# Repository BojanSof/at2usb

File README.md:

# AT (PS/2) keyboard to USB converter

PIC16F1459 solution for converting old AT (PS/2) keyboard to USB.

## Hardware

Schematic and one layer PCB can be found under `hardware` directory.
The hardware design is created using KiCad 7.0.
The circuit is very simple and it can be created easily on prototyping board.

## Firmware

The firmware is developed with MPLAB X IDE, found under `at2usbClassic.X` directory.
USB stack implementation and main HID app code is based on USB HID keyboard project from [Microchip Libraries for Applications (MLA)](https://www.microchip.com/en-us/tools-resources/develop/libraries/microchip-libraries-for-applications).

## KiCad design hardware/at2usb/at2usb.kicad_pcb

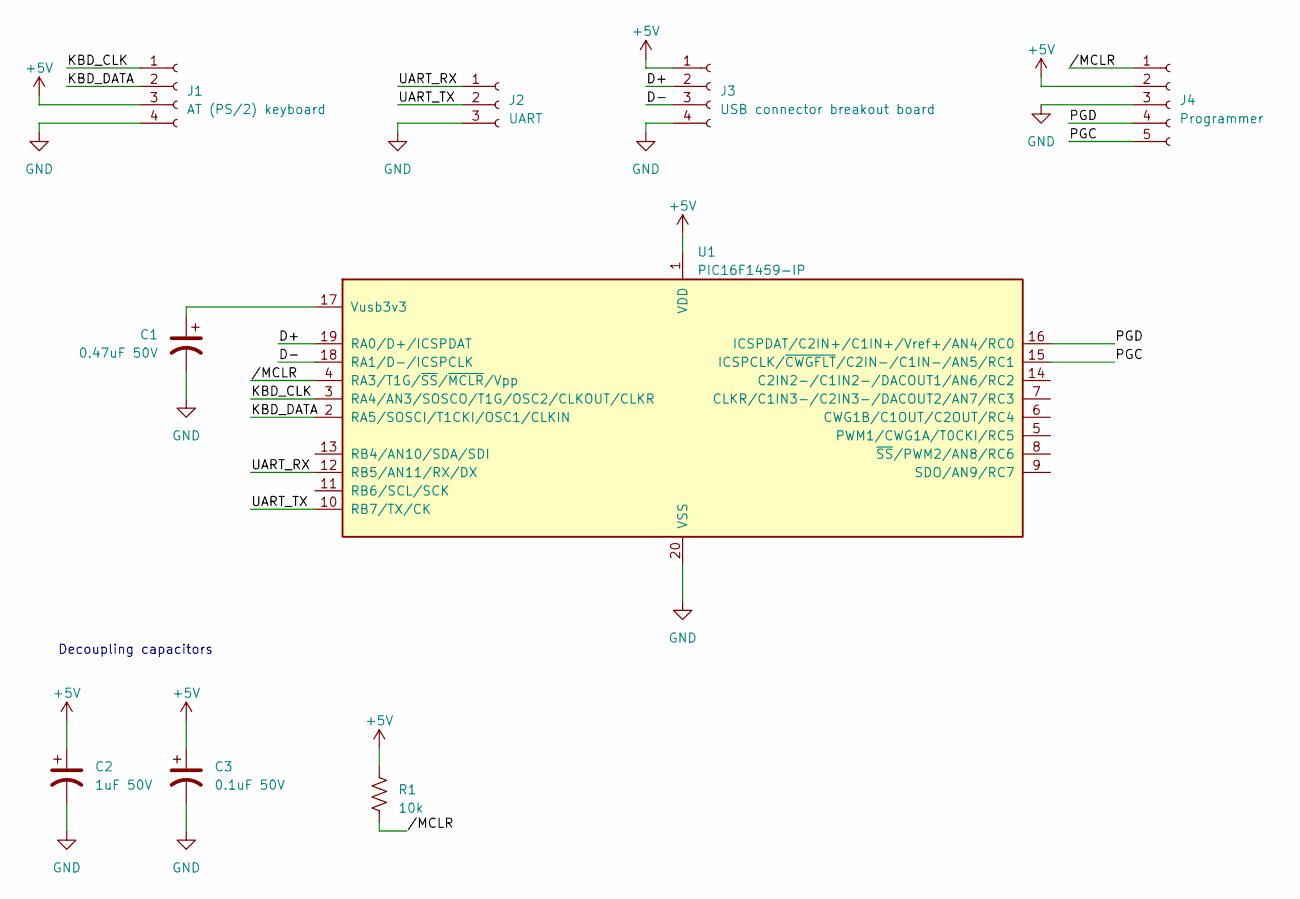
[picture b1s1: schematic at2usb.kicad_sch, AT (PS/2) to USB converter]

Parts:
C1: 0.47uF 50V; CP_Radial_D5.0mm_P2.00mm
C2: 1uF 50V; CP_Radial_D5.0mm_P2.00mm
C3: 0.1uF 50V; CP_Radial_D5.0mm_P2.00mm
J1: AT (PS/2) keyboard; PinHeader_1x04_P2.54mm_Vertical
J2: UART; PinHeader_1x03_P2.54mm_Vertical
J3: USB connector breakout board; PinHeader_1x04_P2.54mm_Vertical
J4: Programmer; PinHeader_1x05_P2.54mm_Vertical
R1: 10k; R_Axial_DIN0207_L6.3mm_D2.5mm_P2.54mm_Vertical
U1: PIC16F1459-IP; DIP-20_W7.62mm_Socket

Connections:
+5V: C2.1, C3.1, J1.3, J3.1, J4.2, R1.1, U1.1 (VDD)
/D+: J3.2, U1.19 (RA0/D+/ICSPDAT)
/D-: J3.3, U1.18 (RA1/D-/ICSPCLK)
/KBD_CLK: J1.1, U1.3 (RA4/AN3/SOSCO/T1G/OSC2/CLKOUT/CLKR)
/KBD_DATA: J1.2, U1.2 (RA5/SOSCI/T1CKI/OSC1/CLKIN)
/PGC: J4.5, U1.15 (ICSPCLK/~CWGFLT/C2IN-/C1IN-/AN5/RC1)
/PGD: J4.4, U1.16 (ICSPDAT/C2IN+/C1IN+/Vref+/AN4/RC0)
/UART_RX: J2.1, U1.12 (RB5/AN11/RX/DX)
/UART_TX: J2.2, U1.10 (RB7/TX/CK)
//MCLR: J4.1, R1.2, U1.4 (RA3/T1G/~SS/~MCLR/Vpp)
GND: C1.2, C2.2, C3.2, J1.4, J2.3, J3.4, J4.3, U1.20 (VSS)
unnamed: C1.1, U1.17 (Vusb3v3)

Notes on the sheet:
Decoupling capacitors

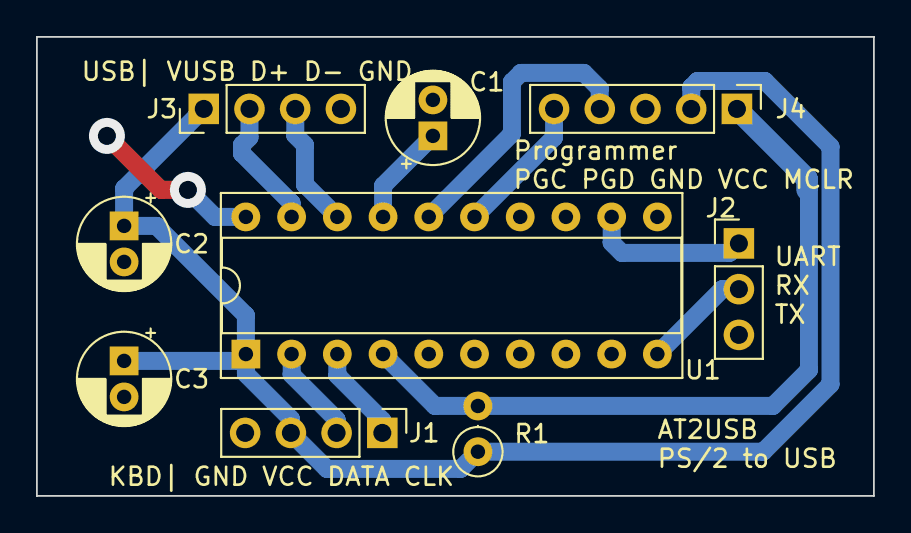
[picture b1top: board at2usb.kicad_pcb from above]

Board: 2 copper layers, 46.5 x 25.5 mm, 9 parts (0 on the bottom side), 12 nets.

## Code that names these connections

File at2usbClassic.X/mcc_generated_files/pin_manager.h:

/**
  @Generated Pin Manager Header File

  @Company:
    Microchip Technology Inc.

  @File Name:
    pin_manager.h

  @Summary:
    This is the Pin Manager file generated using PIC10 / PIC12 / PIC16 / PIC18 MCUs

  @Description
    This header file provides APIs for driver for .
    Generation Information :
        Product Revision  :  PIC10 / PIC12 / PIC16 / PIC18 MCUs - 1.81.8
        Device            :  PIC16F1459
        Driver Version    :  2.11
    The generated drivers are tested against the following:
        Compiler          :  XC8 2.36 and above
        MPLAB 	          :  MPLAB X 6.00	
*/

/*
    (c) 2018 Microchip Technology Inc. and its subsidiaries. 
    
    Subject to your compliance with these terms, you may use Microchip software and any 
    derivatives exclusively with Microchip products. It is your responsibility to comply with third party 
    license terms applicable to your use of third party software (including open source software) that 
    may accompany Microchip software.
    
    THIS SOFTWARE IS SUPPLIED BY MICROCHIP "AS IS". NO WARRANTIES, WHETHER 
    EXPRESS, IMPLIED OR STATUTORY, APPLY TO THIS SOFTWARE, INCLUDING ANY 
    IMPLIED WARRANTIES OF NON-INFRINGEMENT, MERCHANTABILITY, AND FITNESS 
    FOR A PARTICULAR PURPOSE.
    
    IN NO EVENT WILL MICROCHIP BE LIABLE FOR ANY INDIRECT, SPECIAL, PUNITIVE, 
    INCIDENTAL OR CONSEQUENTIAL LOSS, DAMAGE, COST OR EXPENSE OF ANY KIND 
    WHATSOEVER RELATED TO THE SOFTWARE, HOWEVER CAUSED, EVEN IF MICROCHIP 
    HAS BEEN ADVISED OF THE POSSIBILITY OR THE DAMAGES ARE FORESEEABLE. TO 
    THE FULLEST EXTENT ALLOWED BY LAW, MICROCHIP'S TOTAL LIABILITY ON ALL 
    CLAIMS IN ANY WAY RELATED TO THIS SOFTWARE WILL NOT EXCEED THE AMOUNT 
    OF FEES, IF ANY, THAT YOU HAVE PAID DIRECTLY TO MICROCHIP FOR THIS 
    SOFTWARE.
*/

#ifndef PIN_MANAGER_H
#define PIN_MANAGER_H

/**
  Section: Included Files
*/

#include <xc.h>

#define INPUT   1
#define OUTPUT  0

#define HIGH    1
#define LOW     0

#define ANALOG      1
#define DIGITAL     0

#define PULL_UP_ENABLED      1
#define PULL_UP_DISABLED     0

// get/set KBD_CLK aliases
#define KBD_CLK_TRIS                 TRISAbits.TRISA4
#define KBD_CLK_LAT                  LATAbits.LATA4
#define KBD_CLK_PORT                 PORTAbits.RA4
#define KBD_CLK_WPU                  WPUAbits.WPUA4
#define KBD_CLK_ANS                  ANSELAbits.ANSA4
#define KBD_CLK_SetHigh()            do { LATAbits.LATA4 = 1; } while(0)
#define KBD_CLK_SetLow()             do { LATAbits.LATA4 = 0; } while(0)
#define KBD_CLK_Toggle()             do { LATAbits.LATA4 = ~LATAbits.LATA4; } while(0)
#define KBD_CLK_GetValue()           PORTAbits.RA4
#define KBD_CLK_SetDigitalInput()    do { TRISAbits.TRISA4 = 1; } while(0)
#define KBD_CLK_SetDigitalOutput()   do { TRISAbits.TRISA4 = 0; } while(0)
#define KBD_CLK_SetPullup()          do { WPUAbits.WPUA4 = 1; } while(0)
#define KBD_CLK_ResetPullup()        do { WPUAbits.WPUA4 = 0; } while(0)
#define KBD_CLK_SetAnalogMode()      do { ANSELAbits.ANSA4 = 1; } while(0)
#define KBD_CLK_SetDigitalMode()     do { ANSELAbits.ANSA4 = 0; } while(0)

// get/set KBD_DATA aliases
#define KBD_DATA_TRIS                 TRISAbits.TRISA5
#define KBD_DATA_LAT                  LATAbits.LATA5
#define KBD_DATA_PORT                 PORTAbits.RA5
#define KBD_DATA_WPU                  WPUAbits.WPUA5
#define KBD_DATA_SetHigh()            do { LATAbits.LATA5 = 1; } while(0)
#define KBD_DATA_SetLow()             do { LATAbits.LATA5 = 0; } while(0)
#define KBD_DATA_Toggle()             do { LATAbits.LATA5 = ~LATAbits.LATA5; } while(0)
#define KBD_DATA_GetValue()           PORTAbits.RA5
#define KBD_DATA_SetDigitalInput()    do { TRISAbits.TRISA5 = 1; } while(0)
#define KBD_DATA_SetDigitalOutput()   do { TRISAbits.TRISA5 = 0; } while(0)
#define KBD_DATA_SetPullup()          do { WPUAbits.WPUA5 = 1; } while(0)
#define KBD_DATA_ResetPullup()        do { WPUAbits.WPUA5 = 0; } while(0)

// get/set RB7 procedures
#define RB7_SetHigh()            do { LATBbits.LATB7 = 1; } while(0)
#define RB7_SetLow()             do { LATBbits.LATB7 = 0; } while(0)
#define RB7_Toggle()             do { LATBbits.LATB7 = ~LATBbits.LATB7; } while(0)
#define RB7_GetValue()              PORTBbits.RB7
#define RB7_SetDigitalInput()    do { TRISBbits.TRISB7 = 1; } while(0)
#define RB7_SetDigitalOutput()   do { TRISBbits.TRISB7 = 0; } while(0)
#define RB7_SetPullup()             do { WPUBbits.WPUB7 = 1; } while(0)
#define RB7_ResetPullup()           do { WPUBbits.WPUB7 = 0; } while(0)

/**
   @Param
    none
   @Returns
    none
   @Description
    GPIO and peripheral I/O initialization
   @Example
    PIN_MANAGER_Initialize();
 */
void PIN_MANAGER_Initialize (void);

/**
 * @Param
    none
 * @Returns
    none
 * @Description
    Interrupt on Change Handling routine
 * @Example
    PIN_MANAGER_IOC();
 */
void PIN_MANAGER_IOC(void);


/**
 * @Param
    none
 * @Returns
    none
 * @Description
    Interrupt on Change Handler for the IOCAF4 pin functionality
 * @Example
    IOCAF4_ISR();
 */
void IOCAF4_ISR(void);

/**
  @Summary
    Interrupt Handler Setter for IOCAF4 pin interrupt-on-change functionality

  @Description
    Allows selecting an interrupt handler for IOCAF4 at application runtime
    
  @Preconditions
    Pin Manager intializer called

  @Returns
    None.

  @Param
    InterruptHandler function pointer.

  @Example
    PIN_MANAGER_Initialize();
    IOCAF4_SetInterruptHandler(MyInterruptHandler);

*/
void IOCAF4_SetInterruptHandler(void (* InterruptHandler)(void));

/**
  @Summary
    Dynamic Interrupt Handler for IOCAF4 pin

  @Description
    This is a dynamic interrupt handler to be used together with the IOCAF4_SetInterruptHandler() method.
    This handler is called every time the IOCAF4 ISR is executed and allows any function to be registered at runtime.
    
  @Preconditions
    Pin Manager intializer called

  @Returns
    None.

  @Param
    None.

  @Example
    PIN_MANAGER_Initialize();
    IOCAF4_SetInterruptHandler(IOCAF4_InterruptHandler);

*/
extern void (*IOCAF4_InterruptHandler)(void);

/**
  @Summary
    Default Interrupt Handler for IOCAF4 pin

  @Description
    This is a predefined interrupt handler to be used together with the IOCAF4_SetInterruptHandler() method.
    This handler is called every time the IOCAF4 ISR is executed. 
    
  @Preconditions
    Pin Manager intializer called

  @Returns
    None.

  @Param
    None.

  @Example
    PIN_MANAGER_Initialize();
    IOCAF4_SetInterruptHandler(IOCAF4_DefaultInterruptHandler);

*/
void IOCAF4_DefaultInterruptHandler(void);


/**
 * @Param
    none
 * @Returns
    none
 * @Description
    Interrupt on Change Handler for the IOCAF5 pin functionality
 * @Example
    IOCAF5_ISR();
 */
void IOCAF5_ISR(void);

/**
  @Summary
    Interrupt Handler Setter for IOCAF5 pin interrupt-on-change functionality

  @Description
    Allows selecting an interrupt handler for IOCAF5 at application runtime
    
  @Preconditions
    Pin Manager intializer called

  @Returns
    None.

  @Param
    InterruptHandler function pointer.

  @Example
    PIN_MANAGER_Initialize();
    IOCAF5_SetInterruptHandler(MyInterruptHandler);

*/
void IOCAF5_SetInterruptHandler(void (* InterruptHandler)(void));

/**
  @Summary
    Dynamic Interrupt Handler for IOCAF5 pin

  @Description
    This is a dynamic interrupt handler to be used together with the IOCAF5_SetInterruptHandler() method.
    This handler is called every time the IOCAF5 ISR is executed and allows any function to be registered at runtime.
    
  @Preconditions
    Pin Manager intializer called

  @Returns
    None.

  @Param
    None.

  @Example
    PIN_MANAGER_Initialize();
    IOCAF5_SetInterruptHandler(IOCAF5_InterruptHandler);

*/
extern void (*IOCAF5_InterruptHandler)(void);

/**
  @Summary
    Default Interrupt Handler for IOCAF5 pin

  @Description
    This is a predefined interrupt handler to be used together with the IOCAF5_SetInterruptHandler() method.
    This handler is called every time the IOCAF5 ISR is executed. 
    
  @Preconditions
    Pin Manager intializer called

  @Returns
    None.

  @Param
    None.

  @Example
    PIN_MANAGER_Initialize();
    IOCAF5_SetInterruptHandler(IOCAF5_DefaultInterruptHandler);

*/
void IOCAF5_DefaultInterruptHandler(void);



#endif // PIN_MANAGER_H
/**
 End of File
*/

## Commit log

2024-05-06 Fix prev time set for ps2 keyboard reset in case of error
2024-05-06 Add support for sending PS2 commands
2024-05-07 PS2 keyboard leds are only modified from HID output report, fixing compiler warnings
2024-05-07 Add log module, based on EUSART
2024-05-07 Add readme
2024-05-07 Add hardware design in KiCad, update Readme with more brief info
2024-05-19 Add gnd pin next to uart pins
2024-05-20 Add MCLR pull-up resistor in schematic, remove UART RX
2024-05-21 Disable BOR, change USB descriptor, add delay after init
2024-07-21 Add image of keyboard used for development of the project
